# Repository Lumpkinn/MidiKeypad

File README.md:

<h1>MidiKeypad</h1>
A small Midi Keypad made for Hack Club's Half-Life!

(Here's a photo of the PCB!)

(And here's a picture of the design for the PCB, if you wanted to take a closer look!)

<h2>Overview</h2>
This project is a small, instrument made with capacitative pads. You are meant to touch the pads, and use the keys to play specific notes. 

The project itself is based off of <a href="https://github.com/KaiPereira/MIDI-Keypad">KaiPereira's MIDI Keypad</a>!

There are currently no large deviations from his project present, however, some indicator lights for specific notes are currently in the works.

<h3>Attribution</h3>
No AI was used

All art was made by me

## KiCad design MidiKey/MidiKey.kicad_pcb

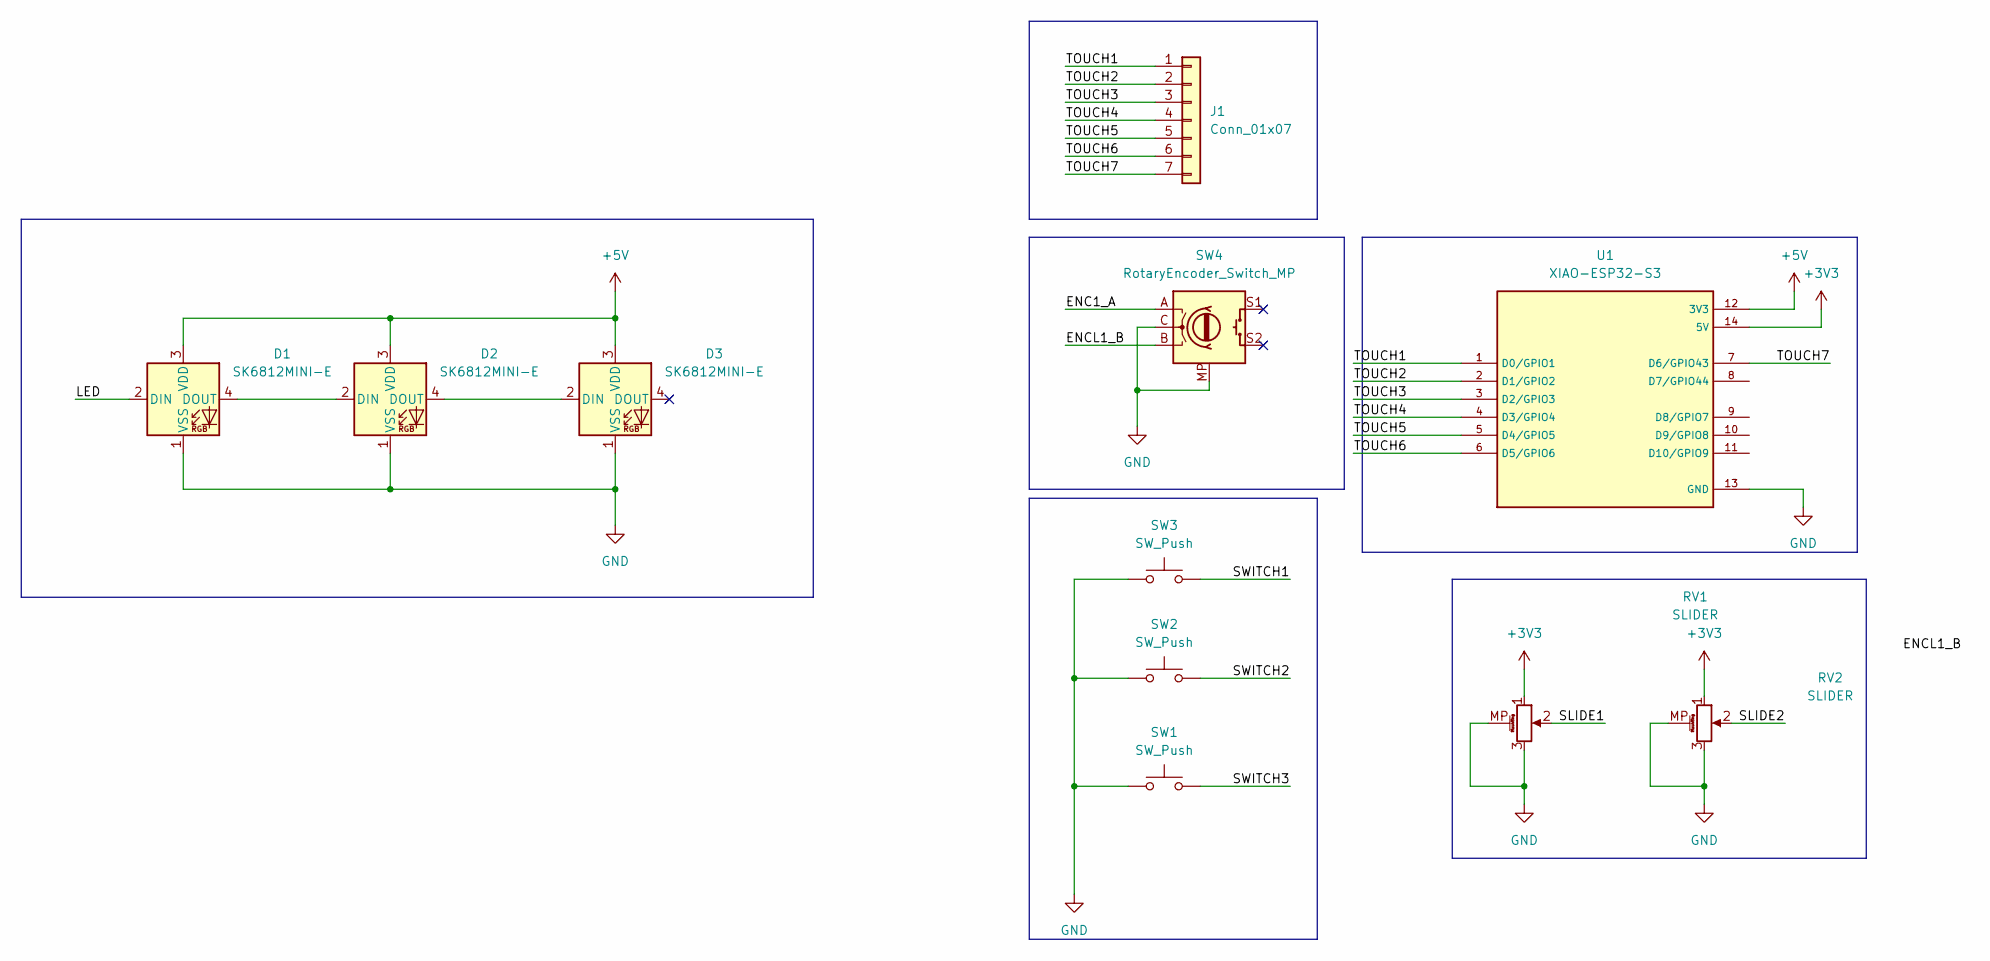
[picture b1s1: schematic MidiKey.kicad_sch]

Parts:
D1, D2, D3: SK6812MINI-E; LED_SK6812MINI-E_3.2x2.8mm_P1.5mm_ReverseMount
J1: Conn_01x07; TSSOP-16_4.4x5mm_P0.65mm
RV1, RV2: SLIDER; Potentiometer_Bourns_PTA1543_Single_Slide
SW1, SW2, SW3: SW_Push; Kailh Choc Low-Profile Switches
SW4: RotaryEncoder_Switch_MP; RotaryEncoder_Alps_EC11E-Switch_Vertical_H20mm
U1: XIAO-ESP32-S3; XIAO ESP32-S3; PARTREV April 22nd, 2026

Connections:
+3V3: RV1.1, RV2.1, U1.14 (5V)
+5V: D1.3 (VDD), D2.3 (VDD), D3.3 (VDD), U1.12 (3V3)
/ENC1_A: SW4.A
/ENCL1_B: SW4.B
/LED: D1.2 (DIN)
/SLIDE1: RV1.2
/SLIDE2: RV2.2
/SWITCH1: SW3.2
/SWITCH2: SW2.2
/SWITCH3: SW1.2
/TOUCH1: J1.1, U1.1 (D0/GPIO1)
/TOUCH2: J1.2, U1.2 (D1/GPIO2)
/TOUCH3: J1.3, U1.3 (D2/GPIO3)
/TOUCH4: J1.4, U1.4 (D3/GPIO4)
/TOUCH5: J1.5, U1.5 (D4/GPIO5)
/TOUCH6: J1.6, U1.6 (D5/GPIO6)
/TOUCH7: J1.7, U1.7 (D6/GPIO43)
GND: D1.1 (VSS), D2.1 (VSS), D3.1 (VSS), RV1.3, RV1.MP (MountPin), RV2.3, RV2.MP (MountPin), SW1.1, SW2.1, SW3.1, SW4.C, SW4.MP, U1.13 (GND)
unnamed: D1.4 (DOUT), D2.2 (DIN)
unnamed: D2.4 (DOUT), D3.2 (DIN)

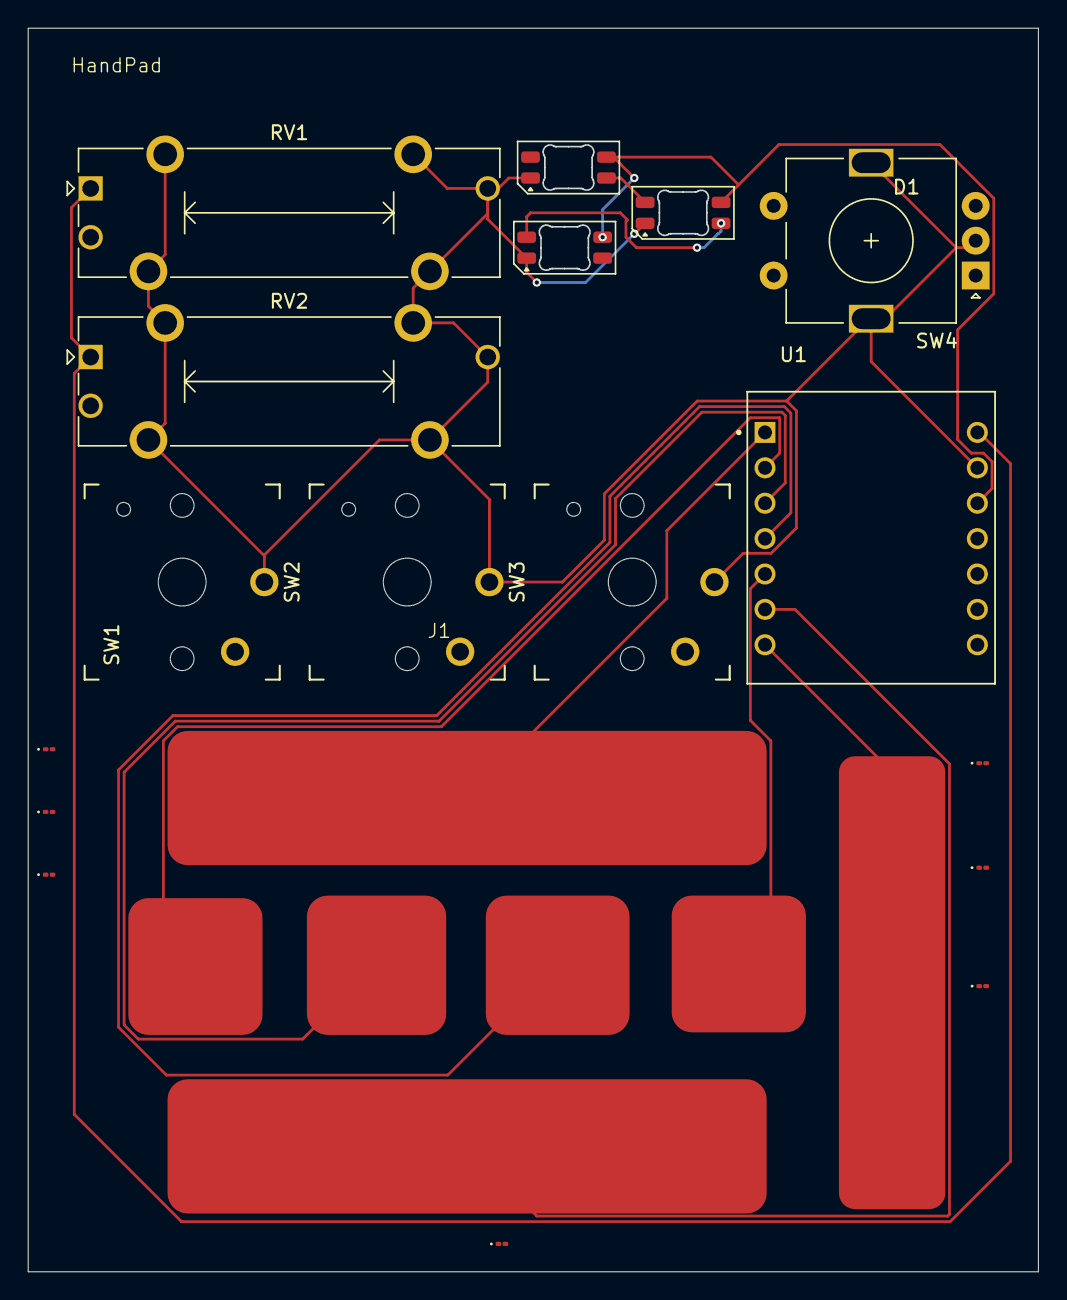
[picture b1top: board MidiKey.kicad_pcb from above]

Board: 2 copper layers, 72.5 x 89.2 mm, 11 parts (0 on the bottom side), 12 nets.

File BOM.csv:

Designator,Footprint,Quantity,Value,Total Cost,Part
"D1, D2, D3",LED_SK6812MINI-E_3.2x2.8mm_P1.5mm_ReverseMount,3,SK6812MINI-E,$3.36,https://www.aliexpress.us/item/3256807677321116.html?spm=a2g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
J1,Capacitive Keys,1,Capacitive Touch Buttons,$4.00,https://cart.jlcpcb.com/quote?quoteTab=standardPcb
"RV1, RV2",Potentiometer_Bourns_PTA1543_Single_Slide,2,Slider,$3.16,https://www.digikey.com/en/products/detail/bourns-inc/PTA154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
"SW1, SW2, SW3",Kailh Choc Low-Profile Switches,3,SW_Push,$6.04,https://www.aliexpress.com/item/1005008883418065.html?spm=a2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
SW4,RotaryEncoder_Alps_EC11E-Switch_Vertical_H20mm,1,RotaryEncoder_Switch_MP,$1.44,https://www.aliexpress.us/item/3256807457768762.html?spm=a2g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
@@ -10,4 +10,4 @@ U1, ESP32-S3-Zero ,1, ESP32-S3-ZERO,$7.49,https://www.seeedstudio.com/XIAO-ESP32
,,,Total Digikey:,$12.35,
,,,Total JLCPCB: ,$4.00,
,,,Total seeedstudio: ,$7.49,
,,,Total:,$24.19,
